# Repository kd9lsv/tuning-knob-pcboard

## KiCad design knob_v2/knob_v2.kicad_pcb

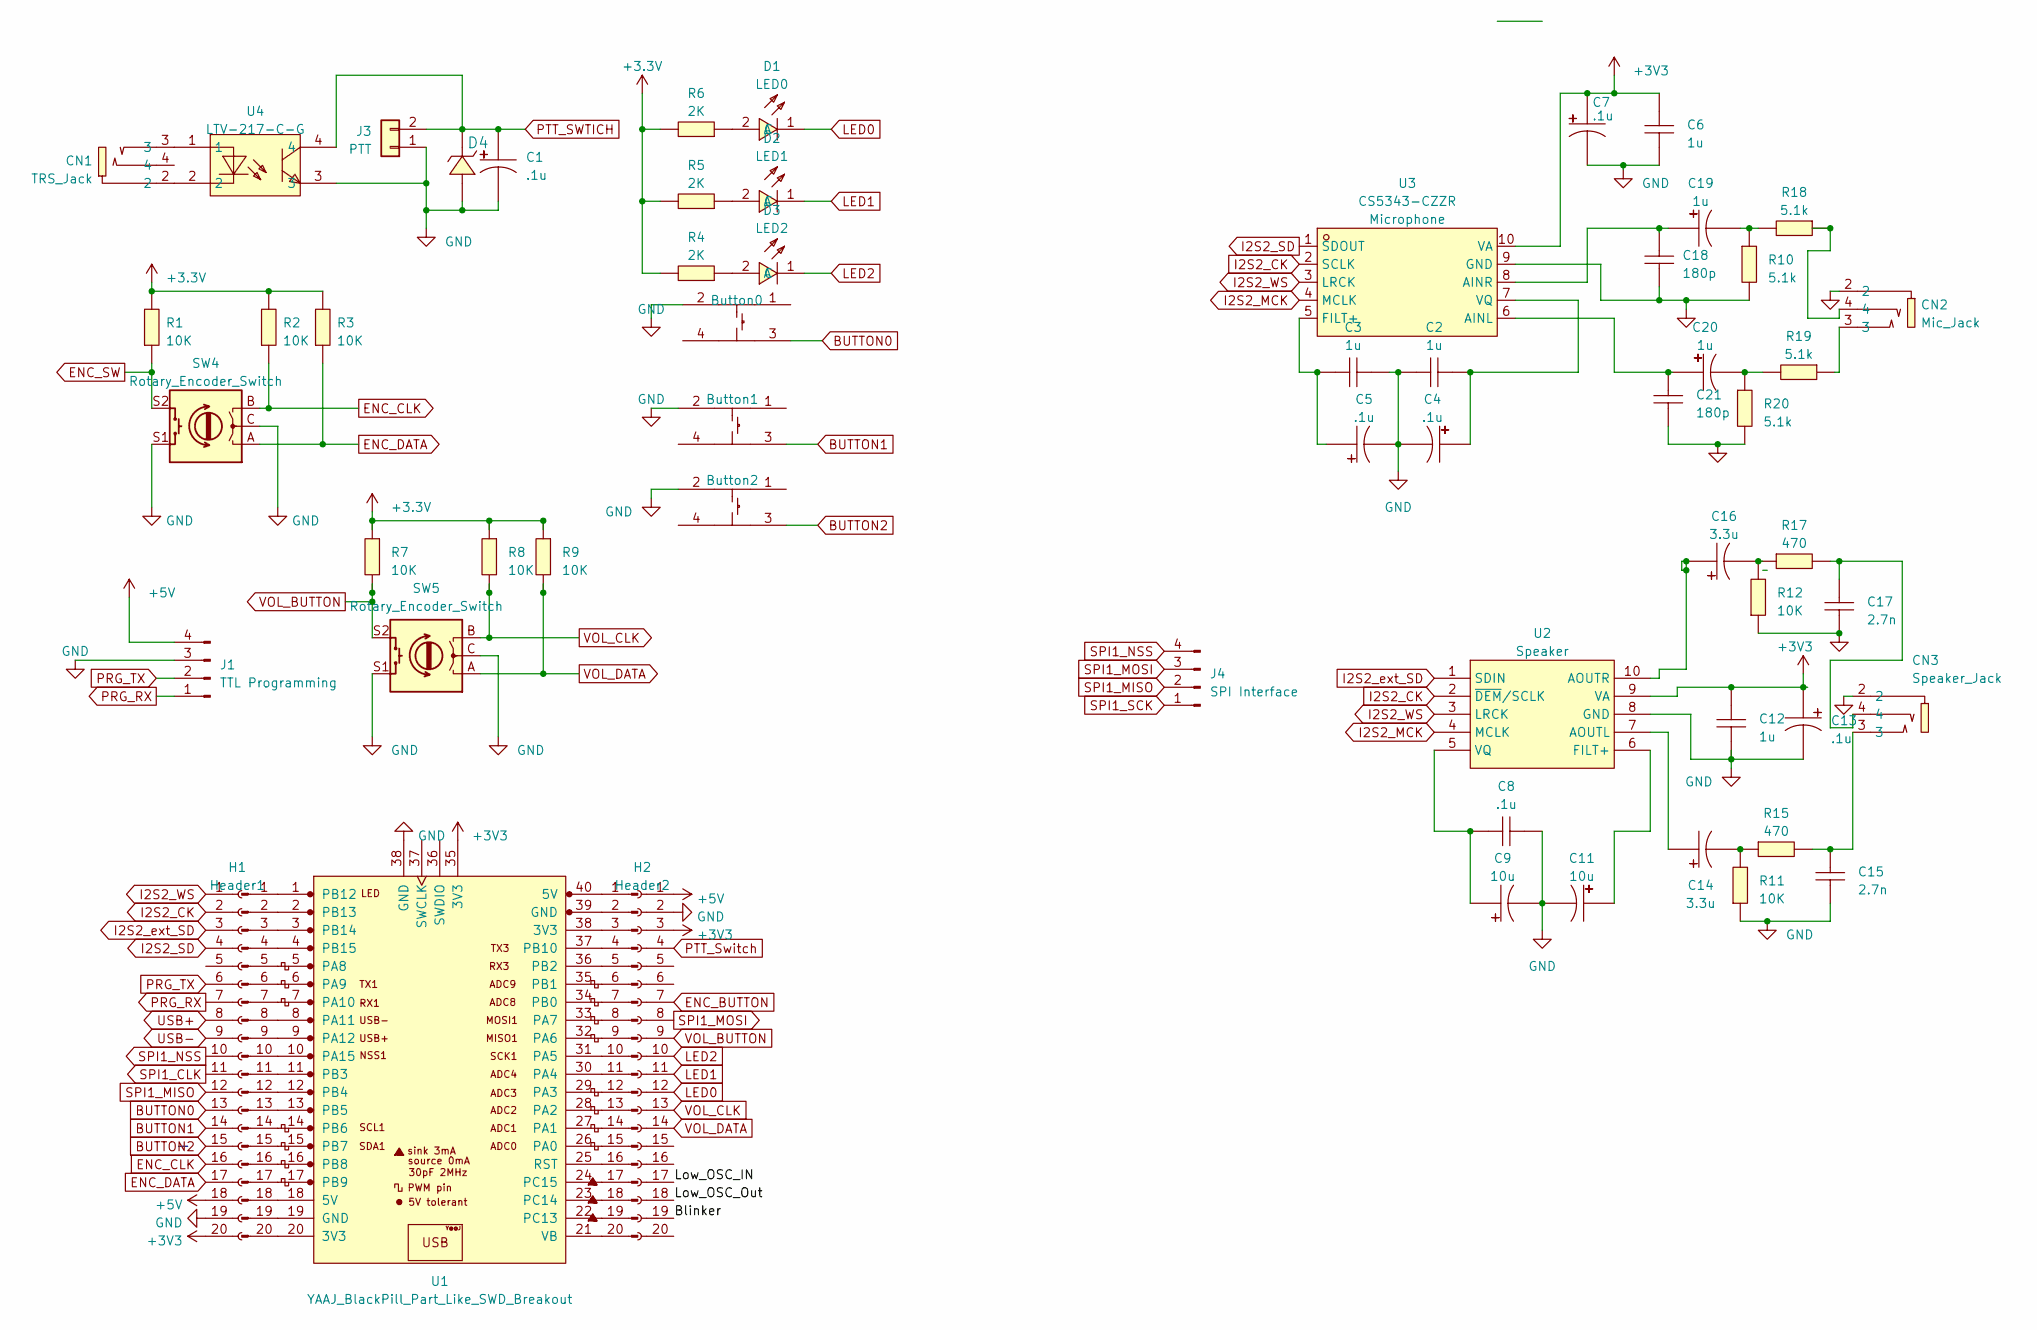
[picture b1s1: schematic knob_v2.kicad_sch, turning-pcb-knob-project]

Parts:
C1, C4, C5, C7, C13: .1u; CAP-SMD_BD4.0-L4.3-W4.3-FD; LCSC Part C271438
C2, C3, C6, C12: 1u; C0805; LCSC Part C519978
C8: .1u; C0805; LCSC Part C126469
C9, C11: 10u; CAP-SMD_BD5.0-L5.3-W5.3-FD; LCSC Part C280395
C14, C16: 3.3u; CAP-SMD_BD4.0-L4.3-W4.3-FD; LCSC Part C413533
C15, C17: 2.7n; C0603; LCSC Part C107085
C18, C21: 180p; C0603; LCSC Part C107041
C19, C20: 1u; CAP-SMD_BD4.0-L4.3-W4.3-FD; LCSC Part C271438
CN1: TRS_Jack; AUDIO-SMD_HOOYA_PJ-326; LCSC Part C2939156
CN2: Mic_Jack; AUDIO-SMD_HOOYA_PJ-326; LCSC Part C2939156
CN3: Speaker_Jack; AUDIO-SMD_HOOYA_PJ-326; LCSC Part C2939156
D1: LED0; LED0603-RD; LCSC Part C72043
D2: LED1; LED0603-RD; LCSC Part C72043
D3: LED2; LED0603-RD; LCSC Part C72043
D4: ZMM5V1_C707194; LL-34_L3.5-W1.5-RD; MPN 1N5231BTR; Digi-Key_PN 1N5231BFSCT-ND
H1: Header1; PinHeader_1x20_P2.54mm_Vertical
H2: Header2; PinHeader_1x20_P2.54mm_Vertical
J1: TTL Programming; PinHeader_1x04_P2.54mm_Vertical
J2, J5: Conn_01x20_Pin
J3: PTT; PinHeader_1x02_P2.54mm_Horizontal
J4: SPI Interface; PinHeader_1x04_P2.54mm_Vertical
R1, R2, R3, R7, R8, R9, R11, R12: 0805W8F1002T5E; R0805; LCSC Part C17414
R4, R5, R6: 2K; R0805; LCSC Part C17604
R10, R18, R19, R20: 5.1k; R0805; LCSC Part C204548
R15, R17: 470; R0805; LCSC Part C17710
SW1: Button0; KEY-TH_4P-L12.0-W12.0-P5.00-LS12.5; LCSC Part C455216
SW2: Button1; KEY-TH_4P-L12.0-W12.0-P5.00-LS12.5; LCSC Part C455216
SW3: Button2; KEY-TH_4P-L12.0-W12.0-P5.00-LS12.5; LCSC Part C455216
SW4, SW5: Rotary_Encoder_Switch; RotaryEncoder_Alps_EC12E-Switch_Vertical_H20mm
U1: YAAJ_BlackPill_Part_Like_SWD_Breakout
U2: Speaker; TSSOP-10_L3.0-W3.0-P0.50-LS4.9-BL; LCSC Part C8952
U3: CS5343-CZZR; TSSOP-10_L3.0-W3.0-P0.50-LS4.9-BL; LCSC Part C323607
U4: LTV-217-C-G; SMD-4_L2.7-W4.4-P1.27-LS7.0-BL; LCSC Part C123196

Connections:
+5V: H1.18, H2.1, J1.4
/Blinker: H2.19
/Low_OSC_IN: H2.17
/Low_OSC_Out: H2.18
BUTTON0: H1.13, SW1.3
BUTTON1: H1.14, SW2.3
BUTTON2: H1.15, SW3.3
ENC_BUTTON: H2.7
ENC_CLK: H1.16, R2.1, SW4.B
ENC_DATA: H1.17, R3.1, SW4.A
ENC_SW: R1.1, SW4.S2
GND: C1.1, C2.1, C3.2, C4.1, C5.1, C6.2, C7.1, C8.2, C9.2, C11.2, C12.1, C13.1, C15.1, C17.1, C18.2, C21.2, CN2.2, CN3.2, D4.2 (A), H1.19, H2.2, J1.3, J3.1, R10.2, R11.1, R12.1, R20.2, SW1.2, SW2.2, SW3.2, SW4.C, SW4.S1, SW5.C, SW5.S1, U1.38 (3V3), U2.8 (GND), U3.9 (GND), U4.3
I2S2_CK: H1.2, U2.2 (~DEM/SCLK), U3.2 (SCLK)
I2S2_MCK: U2.4 (MCLK), U3.4 (MCLK)
I2S2_SD: H1.4, U3.1 (SDOUT)
I2S2_WS: H1.1, U2.3 (LRCK), U3.3 (LRCK)
I2S2_ext_SD: H1.3, U2.1 (SDIN)
LED0: D1.1 (C), H2.12
LED1: D2.1 (C), H2.11
LED2: D3.1 (C), H2.10
unnamed: C14.1, R11.2, R15.1
unnamed: C15.2, CN3.3, R15.2
unnamed: C16.1, R12.2, R17.1
unnamed: C17.2, CN3.4, R17.2
unnamed: C19.1, R10.1, R18.2
unnamed: C20.1, R19.2, R20.1
unnamed: CN1.2, U4.2
unnamed: CN1.3, U4.1
unnamed: CN2.3, R19.1
unnamed: CN2.4, R18.1
unnamed: D1.2 (A), R6.1
unnamed: D2.2 (A), R5.1
unnamed: D3.2 (A), R4.1
unnamed: J2.1, U1.1 (PB12)
unnamed: J2.2, U1.2 (PB13)
unnamed: J2.3, U1.3 (PB14)
unnamed: J2.4, U1.4 (PB15)
unnamed: J2.5, U1.5 (PA8)
unnamed: J2.6, U1.6 (PA9)
unnamed: J2.7, U1.7 (PA10)
unnamed: J2.8, U1.8 (PA11)
unnamed: J2.9, U1.9 (PA12)
unnamed: J2.10, U1.10 (PA15)
unnamed: J2.11, U1.11 (PB3)
unnamed: J2.12, U1.12 (PB4)
unnamed: J2.13, U1.13 (PB5)
unnamed: J2.14, U1.14 (PB6)
unnamed: J2.15, U1.15 (PB7)
unnamed: J2.16, U1.16 (PB8)
unnamed: J2.17, U1.17 (PB9)
unnamed: J2.18, U1.18 (5V)
unnamed: J2.19, U1.19 (GND)
unnamed: J2.20, U1.20 (3V3)
unnamed: J5.1, U1.40 (5V)
unnamed: J5.2, U1.39 (GND)
unnamed: J5.3, U1.38 (3V3)
unnamed: J5.4, U1.37 (PB10)
unnamed: J5.5, U1.36 (PB2)
unnamed: J5.6, U1.35 (3V3)
unnamed: J5.7, U1.34 (PB0)
unnamed: J5.8, U1.33 (PA7)
unnamed: J5.9, U1.32 (PA6)
unnamed: J5.10, U1.31 (PA5)
unnamed: J5.11, U1.30 (PA4)
unnamed: J5.12, U1.29 (PA3)
unnamed: J5.13, U1.28 (PA2)
unnamed: J5.14, U1.27 (PA1)
unnamed: J5.15, U1.26 (PA0)
unnamed: J5.16, U1.25 (RST)
unnamed: J5.17, U1.24 (PC15)
unnamed: J5.18, U1.23 (PC14)
unnamed: J5.19, U1.22 (PC13)
unnamed: J5.20, U1.21 (VB)
unnamed: C14.2, U2.7 (AOUTL)
unnamed: C16.2, U2.10 (AOUTR)
unnamed: C11.1, U2.6 (FILT+)
unnamed: C8.1, C9.1, U2.5 (VQ)
unnamed: C20.2, C21.1, U3.6 (AINL)
unnamed: C18.1, C19.2, U3.8 (AINR)
unnamed: C3.1, C5.2, U3.5 (FILT+)
unnamed: C2.2, C4.2, U3.7 (VQ)
PRG_RX: H1.7, J1.1
PRG_TX: H1.6, J1.2
PTT_SWTICH: C1.2, D4.1 (C), J3.2, U4.4
PTT_Switch: H2.4
SPI1_CLK: H1.11
SPI1_MISO: H1.12, J4.2
SPI1_MOSI: H2.8, J4.3
SPI1_NSS: H1.10, J4.4
SPI1_SCK: J4.1
USB+: H1.8
USB-: H1.9
VOL_BUTTON: H2.9, R7.2, SW5.S2
VOL_CLK: H2.13, R8.2, SW5.B
VOL_DATA: H2.14, R9.2, SW5.A

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
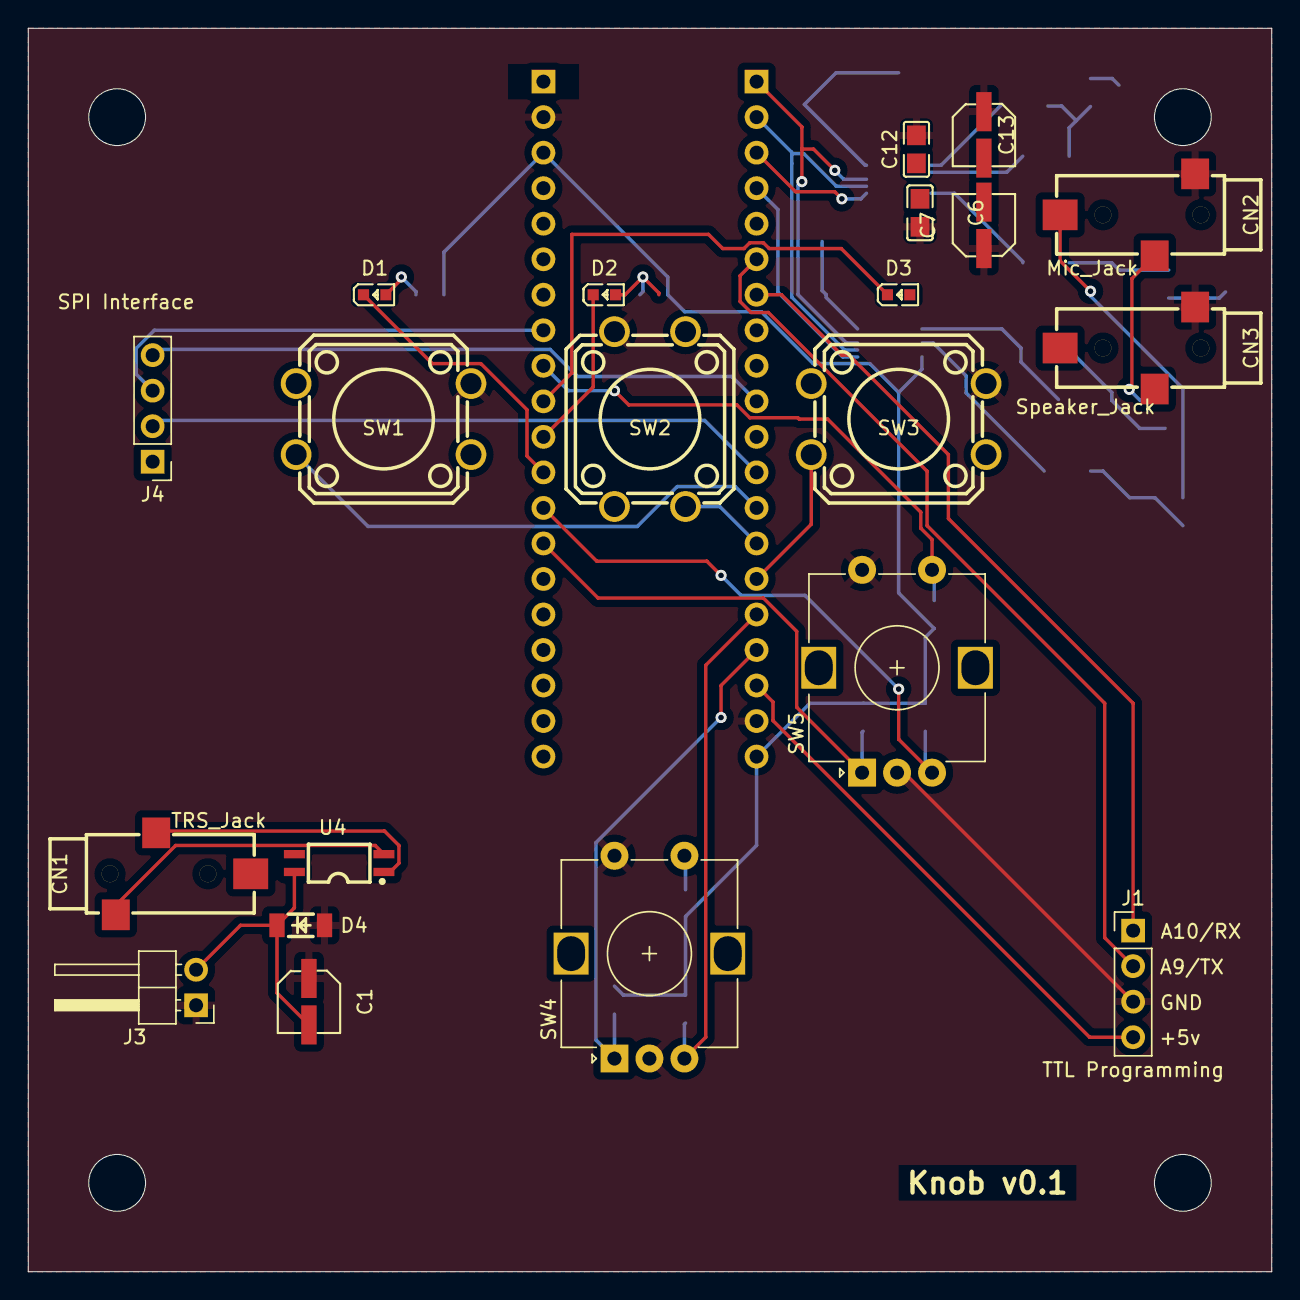
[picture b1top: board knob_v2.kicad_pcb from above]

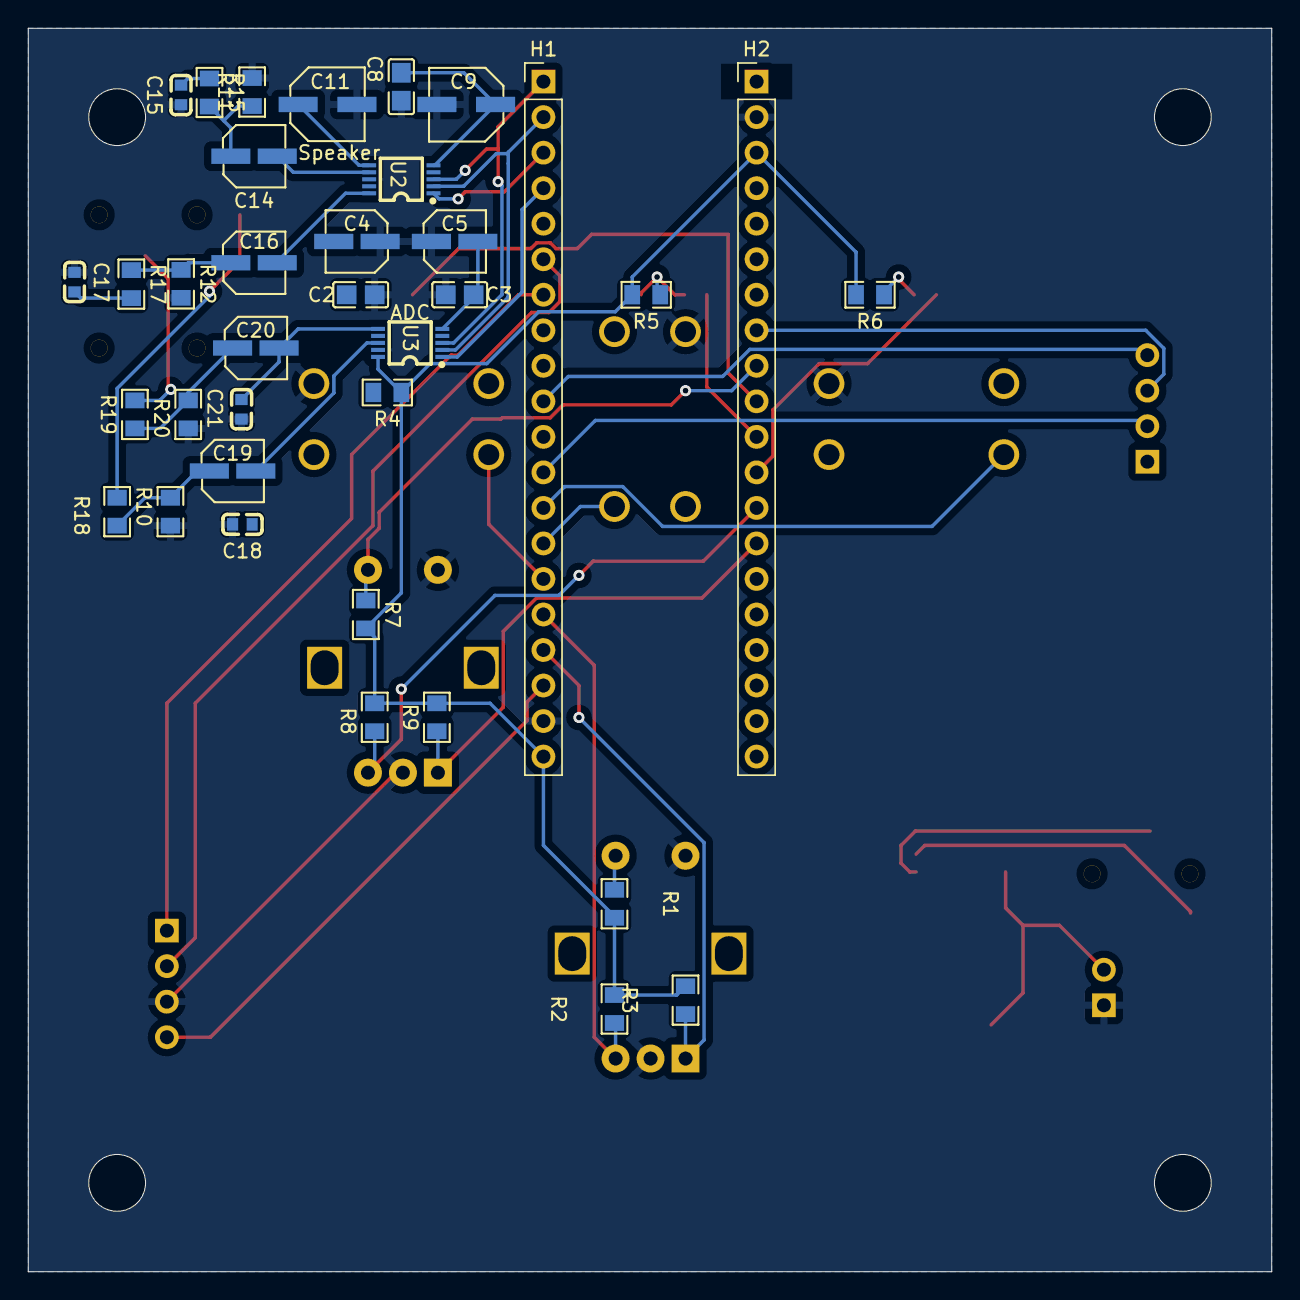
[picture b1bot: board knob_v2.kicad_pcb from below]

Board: 2 copper layers, 88.9 x 88.9 mm, 57 parts (36 on the bottom side), 47 nets.

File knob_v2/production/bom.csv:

Designator,Footprint,Quantity,Value,LCSC Part #
"C1, C13, C4, C5, C7",CAP-SMD_BD4.0-L4.3-W4.3-FD,5,.1u,C271438
"C11, C9",CAP-SMD_BD5.0-L5.3-W5.3-FD,2,10u,C280395
"C12, C2, C3, C6",C0805,4,1u,C519978
"C14, C16",CAP-SMD_BD4.0-L4.3-W4.3-FD,2,3.3u,C413533
"C15, C17",C0603,2,2.7n,C107085
"C18, C21",C0603,2,180p,C107041
"C19, C20",CAP-SMD_BD4.0-L4.3-W4.3-FD,2,1u,C271438
C8,C0805,1,.1u,C126469
CN1,AUDIO-SMD_HOOYA_PJ-326,1,TRS_Jack,C2939156
CN2,AUDIO-SMD_HOOYA_PJ-326,1,Mic_Jack,C2939156
CN3,AUDIO-SMD_HOOYA_PJ-326,1,Speaker_Jack,C2939156
D1,LED0603-RD,1,LED0,C72043
D2,LED0603-RD,1,LED1,C72043
D3,LED0603-RD,1,LED2,C72043
D4,LL-34_L3.5-W1.5-RD,1,ZMM5V1_C707194,C707194
H1,PinHeader_1x20_P2.54mm_Vertical,1,Header1,
H2,PinHeader_1x20_P2.54mm_Vertical,1,Header2,
J1,PinHeader_1x04_P2.54mm_Vertical,1,TTL Programming,
J3,PinHeader_1x02_P2.54mm_Horizontal,1,PTT,
J4,PinHeader_1x04_P2.54mm_Vertical,1,SPI Interface,
"R1, R11, R12, R2, R3, R7, R8, R9",R0805,8,0805W8F1002T5E,C17414
"R10, R18, R19, R20",R0805,4,5.1k,C204548
"R15, R17",R0805,2,470,C17710
"R4, R5, R6",R0805,3,2K,C17604
SW1,KEY-TH_4P-L12.0-W12.0-P5.00-LS12.5,1,Button0,C455216
SW2,KEY-TH_4P-L12.0-W12.0-P5.00-LS12.5,1,Button1,C455216
SW3,KEY-TH_4P-L12.0-W12.0-P5.00-LS12.5,1,Button2,C455216
"SW4, SW5",RotaryEncoder_Alps_EC12E-Switch_Vertical_H20mm,2,Rotary_Encoder_Switch,
U2,TSSOP-10_L3.0-W3.0-P0.50-LS4.9-BL,1,Speaker,C8952
U3,TSSOP-10_L3.0-W3.0-P0.50-LS4.9-BL,1,CS5343-CZZR,C323607
U4,SMD-4_L2.7-W4.4-P1.27-LS7.0-BL,1,LTV-217-C-G,C123196

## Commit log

2023-06-06 knob_v2 with D/A, A/D, 2 Knobs, and SPI, UART, 3 LEDs w/ switches.
2023-06-07 part2 06/06/2023 add parts to library.
2023-06-08 06/08/2023, Made BOM complete, fixed placement and initial routing..
